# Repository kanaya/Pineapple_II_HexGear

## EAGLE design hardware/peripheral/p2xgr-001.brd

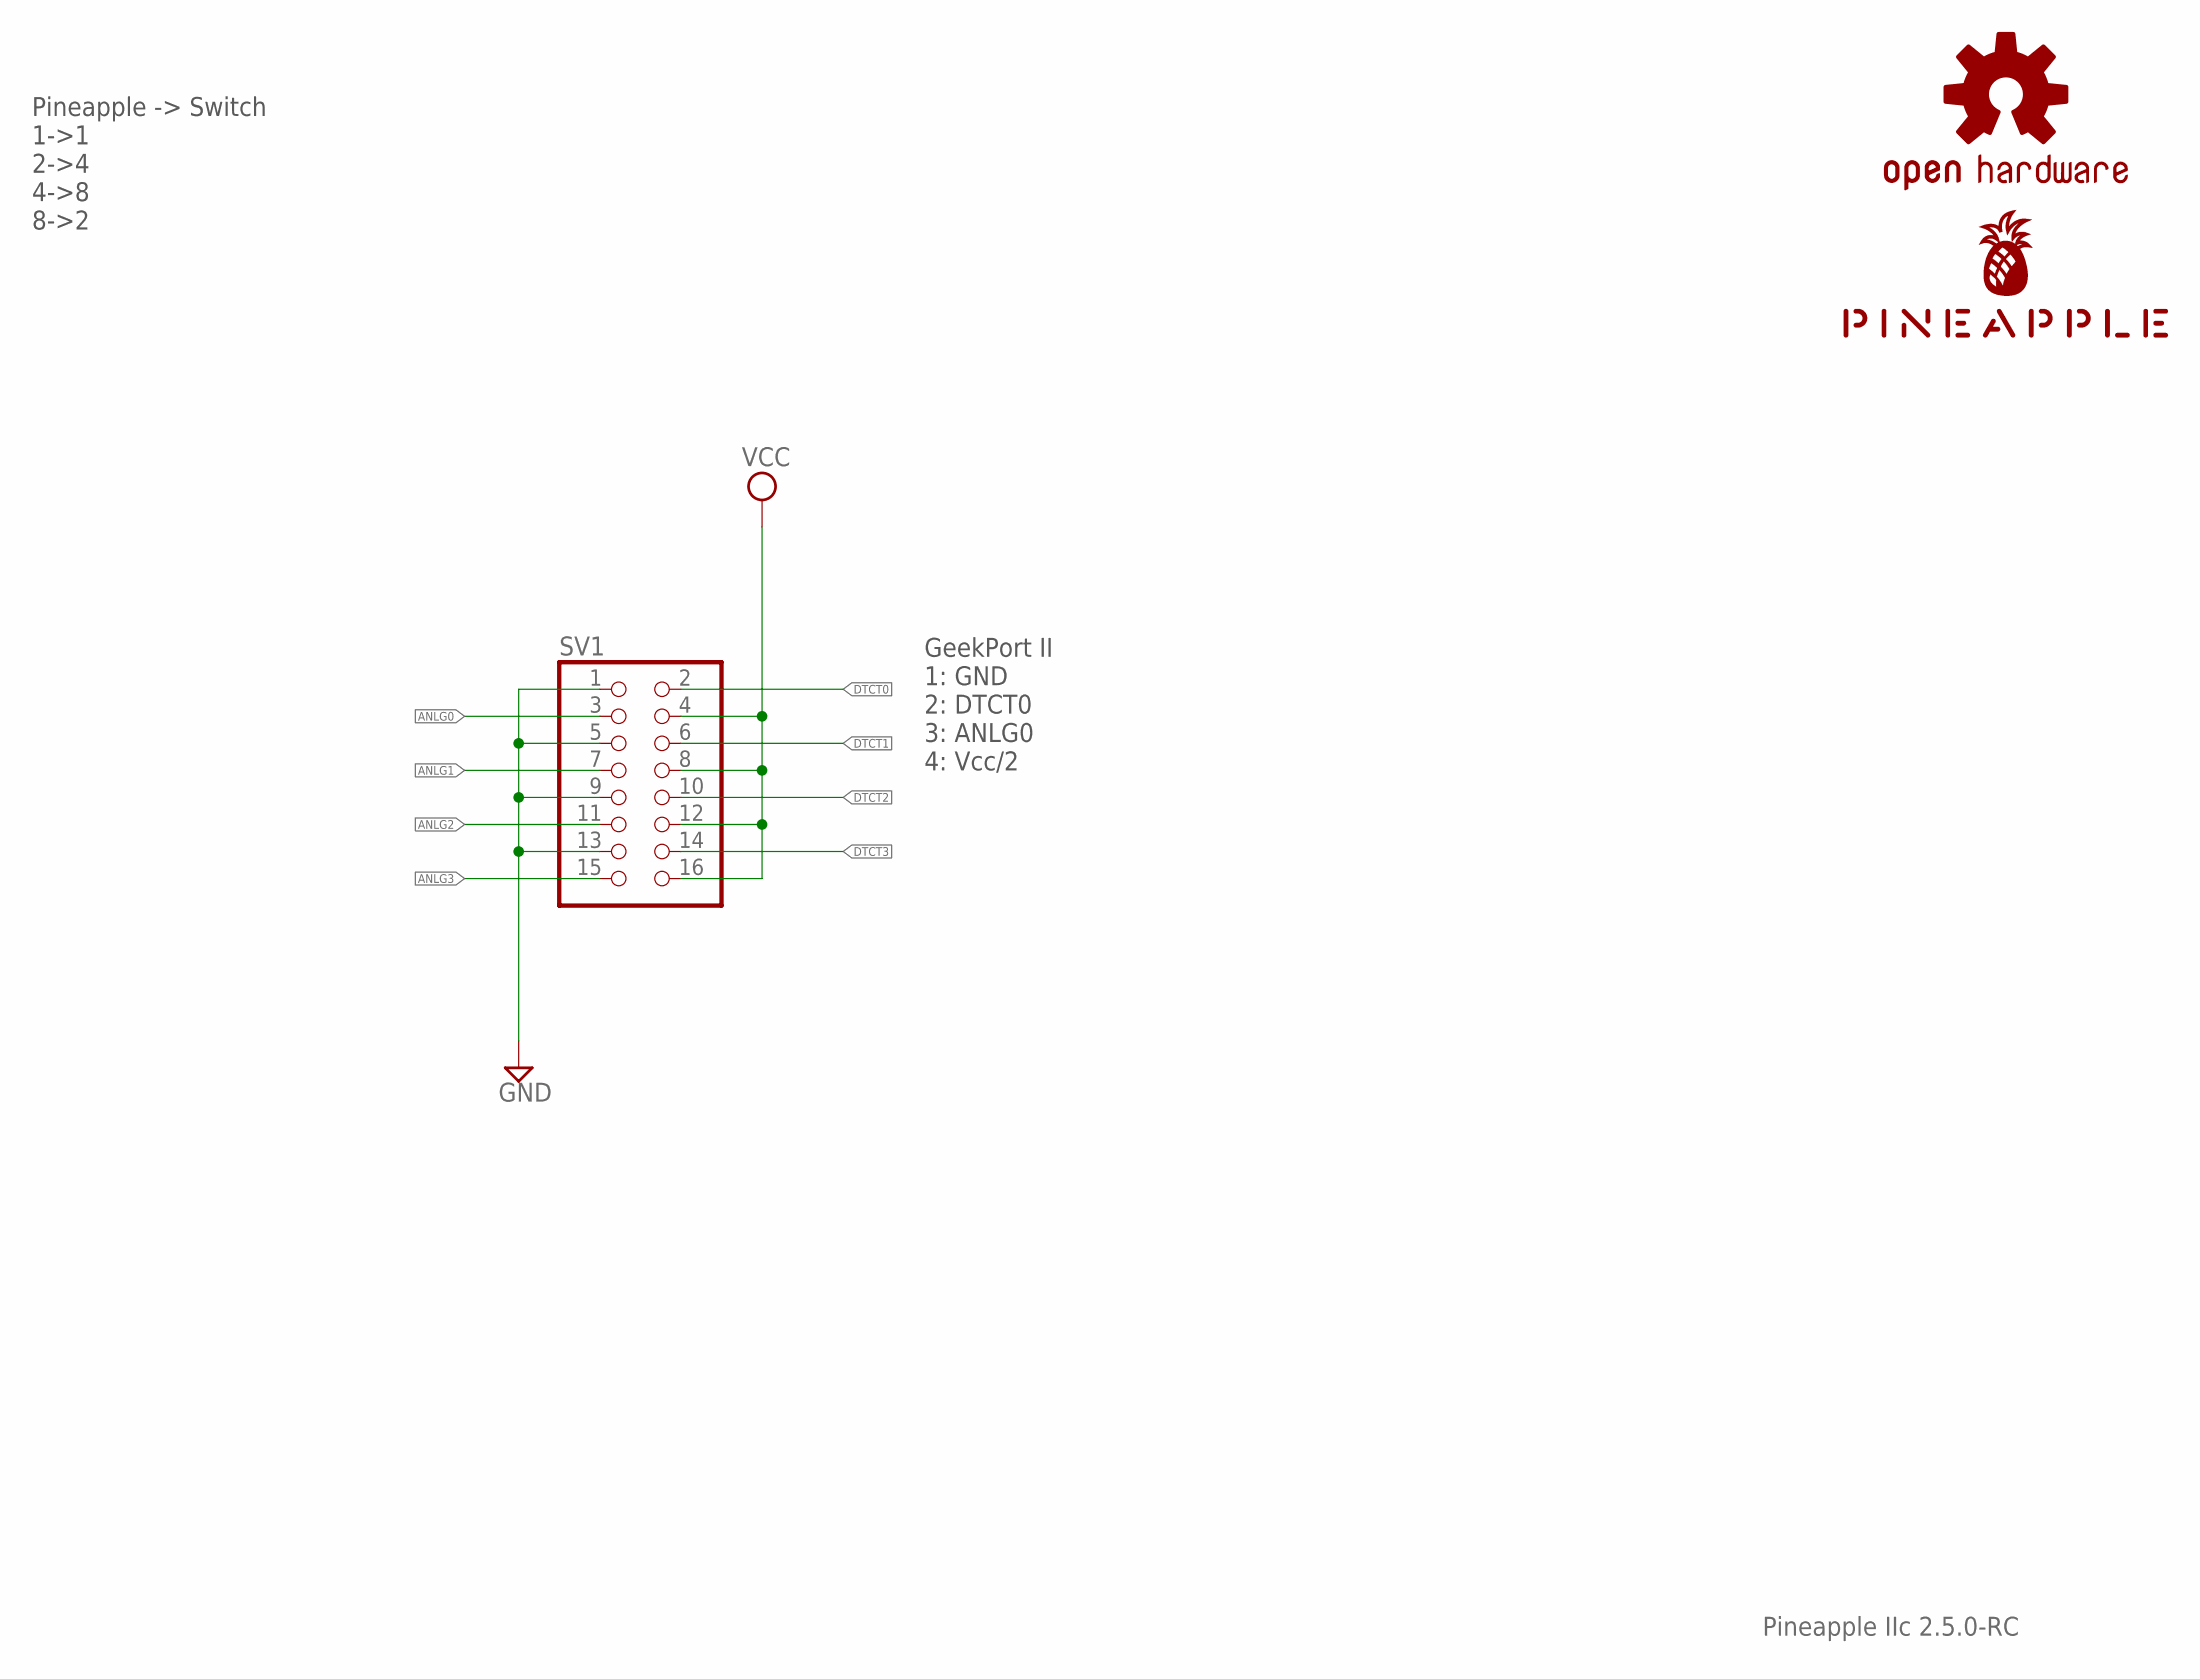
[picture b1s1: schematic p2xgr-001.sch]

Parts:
LOGO1: OSHW-LOGOS-COPPER; OSHW-LOGO-S_COPPER
SV1: PINHD-2X8; 2X08
U$1: PINEAPPLE450_SILK

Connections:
ANLG0: SV1.3
ANLG1: SV1.7
ANLG2: SV1.11
ANLG3: SV1.15
DTCT0: SV1.2
DTCT1: SV1.6
DTCT2: SV1.10
DTCT3: SV1.14
GND: SV1.1, SV1.5, SV1.9, SV1.13
VCC: SV1.4, SV1.8, SV1.12, SV1.16

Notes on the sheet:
Pineapple IIc 2.5.0-RC
Pineapple -> Switch 1->1 2->4 4->8 8->2
GeekPort II 1: GND 2: DTCT0 3: ANLG0 4: Vcc/2

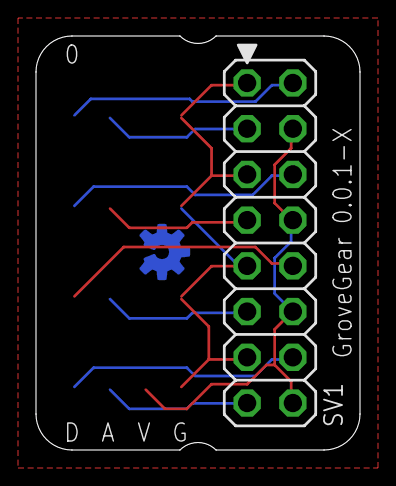
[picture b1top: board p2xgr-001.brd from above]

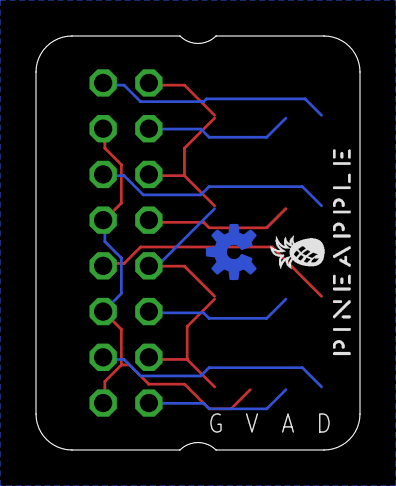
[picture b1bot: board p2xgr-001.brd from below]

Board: 2 copper layers, 18.0 x 23.0 mm, 3 parts (2 on the bottom side), 2 nets.

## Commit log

2022-09-18 Initial commit. (Imported from GroveGear.)
2022-09-18 Clean up.
2022-09-18 First working model.

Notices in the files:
parts and their libraries:
SparkFun-Aesthetics: Licensing: Creative Commons ShareAlike 4.0 International - https://creativecommons.org/licenses/by-sa/4.0
